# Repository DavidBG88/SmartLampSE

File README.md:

# **SmartLampSE**

## **Overview**
This repository contains the code for the Smart Lamp EmbeddedSystem (SmartLampSE) project. The project involves designing and implementing a smart lamp system using various technologies and programming languages.

## **Features**
- **Electronics Design**: Schematics and PCB design for the smart lamp hardware.
- **Software**: Code for controlling the smart lamp, including firmware and higher-level software.
- **System Model**: Models and diagrams illustrating the system architecture and behavior.

## **Structure**
- **electronics_design/**: Contains schematics and PCB design files.
- **software/**: Source code for the smart lamp, including firmware and application software.
- **system_model/**: System architecture models and documentation.
- **.gitignore**: Git ignore file for the repository.

## **Contributors**
- [DavidBG88](https://github.com/DavidBG88)
- [Tikitikitikidesuka](https://github.com/Tikitikitikidesuka)

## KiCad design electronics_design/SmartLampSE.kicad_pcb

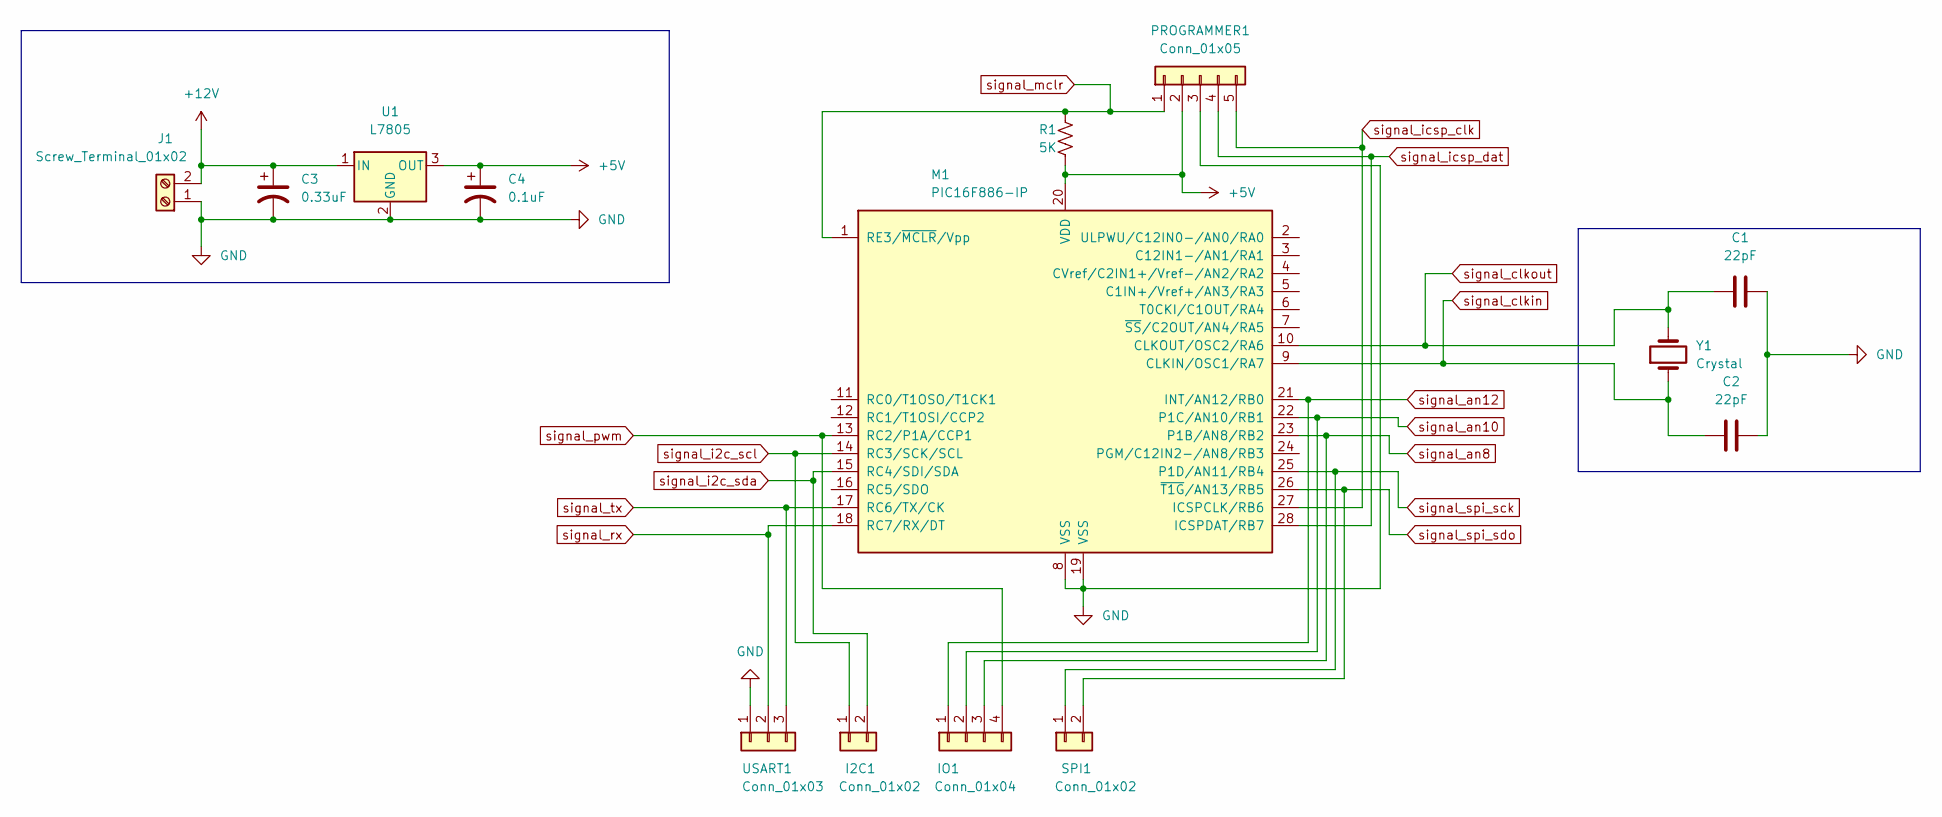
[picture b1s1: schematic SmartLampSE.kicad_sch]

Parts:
C1, C2: 22pF; C_Disc_D3.8mm_W2.6mm_P2.50mm
C3: 0.33uF; CP_Radial_D5.0mm_P2.50mm
C4: 0.1uF; CP_Radial_D5.0mm_P2.50mm
I2C1: Conn_01x02; PinSocket_1x02_P2.54mm_Vertical
IO1: Conn_01x04; PinSocket_1x04_P2.54mm_Vertical
J1: Screw_Terminal_01x02; TerminalBlock_Phoenix_MKDS-1,5-2-5.08_1x02_P5.08mm_Horizont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
M1: PIC16F886-IP; DIP-28_W7.62mm
PROGRAMMER1: Conn_01x05; PinSocket_1x05_P2.54mm_Vertical
R1: 5K; R_Axial_DIN0204_L3.6mm_D1.6mm_P5.08mm_Horizontal
SPI1: Conn_01x02; PinSocket_1x02_P2.54mm_Vertical
U1: L7805; TO-220-3_Vertical
USART1: Conn_01x03; PinSocket_1x03_P2.54mm_Vertical
Y1: Crystal; Crystal_HC18-U_Vertical

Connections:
+5V: C4.1, M1.20 (VDD), PROGRAMMER1.2, R1.2, U1.3 (OUT)
+12V: C3.1, J1.2, U1.1 (IN)
GND: C1.2, C2.2, C3.2, C4.2, J1.1, M1.8 (VSS), M1.19 (VSS), PROGRAMMER1.3, U1.2 (GND), USART1.1
signal_an8: IO1.3, M1.23 (P1B/AN8/RB2)
signal_an10: IO1.2, M1.22 (P1C/AN10/RB1)
signal_an12: IO1.1, M1.21 (INT/AN12/RB0)
signal_clkin: C2.1, M1.9 (CLKIN/OSC1/RA7), Y1.1
signal_clkout: C1.1, M1.10 (CLKOUT/OSC2/RA6), Y1.2
signal_i2c_scl: I2C1.1, M1.14 (RC3/SCK/SCL)
signal_i2c_sda: I2C1.2, M1.15 (RC4/SDI/SDA)
signal_icsp_clk: M1.27 (ICSPCLK/RB6), PROGRAMMER1.5
signal_icsp_dat: M1.28 (ICSPDAT/RB7), PROGRAMMER1.4
signal_mclr: M1.1 (RE3/~MCLR/Vpp), PROGRAMMER1.1, R1.1
signal_pwm: IO1.4, M1.13 (RC2/P1A/CCP1)
signal_rx: M1.18 (RC7/RX/DT), USART1.2
signal_spi_sck: M1.25 (P1D/AN11/RB4), SPI1.1
signal_spi_sdo: M1.26 (~T1G/AN13/RB5), SPI1.2
signal_tx: M1.17 (RC6/TX/CK), USART1.3

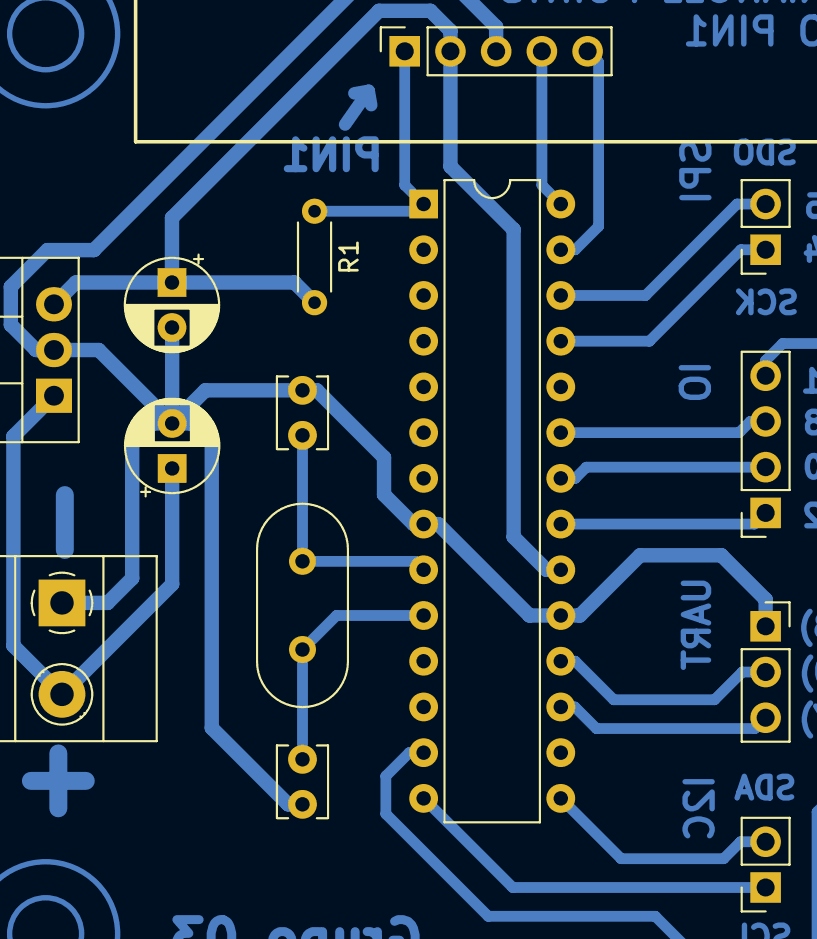
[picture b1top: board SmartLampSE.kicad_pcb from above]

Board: 2 copper layers, 14 parts (0 on the bottom side), 18 nets.

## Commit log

2023-11-05 Add empty Papyrus Sysml project
2023-11-06 Separate board IO interface
2023-11-06 Fix lock files
2023-11-06 Finish pcb pathing
2023-11-07 Update group name on electronics design
2023-11-09 Add visual polarity indicators to board supply
2023-11-10 Fix some widths
2023-11-10 Add MPLab IDE ignored files
2023-11-10 Add MPLab project
2023-11-10 Update gitignore for MPLab projects
2023-11-11 Update pwm library
2023-11-11 Add clang-format file
2023-11-16 Update project model
2023-11-16 Add port connections to system model
2023-11-16 Fix wrong arrow direction in model
2023-11-16 Update ocnnector names in model
2023-11-16 Update model
2023-11-16 Fix typos in pwm header file
2023-11-16 Remove board test libraries
2023-11-16 Update gitignore for new production directory
2023-11-16 Add production smart_lamp_se project
2023-11-16 Added Design.png to electronic Design
2023-11-16 Added tests to main.c for ADC and USART, also notes for I2C future tests
2023-11-17 Fill untested timing implementation
2023-11-18 Fix timing module
2023-11-18 Add State Machine Diagram for controller block
2023-11-18 Update SMD_Controller model
2023-11-18 Refactor model file structure
2023-11-18 Update system model
2023-11-22 Add ADC module
2023-11-22 Fix adc type warning
2023-11-22 Add uart module
2023-11-29 Update state machine in SysML model
2023-11-30 Update uart library
2023-12-01 Update main program
2023-12-01 Fix uart last byte missing error
2023-12-01 Update interrupt flag update policy
2023-12-01 Added I2C test to board_test
2023-12-01 VOID
2023-12-01 Update uart module
2023-12-01 Update UART to remove unnecessary code
2023-12-03 Add i2c library
2023-12-03 Add library for the iAQ-Core sensor
2023-12-03 Add spi library
2023-12-03 Add APA102 RGB LED library
2023-12-03 Add new library files to MPLAB project
2023-12-03 Update ADC module to take adc pin as parameter
2023-12-03 Fix APA102.h include guards
2023-12-03 Add i2c init function
2023-12-03 Remove hyphen from iAQCore library file names
2023-12-03 Update main to follow previous changes
2023-12-03 Add EEPROM memory module
2023-12-03 Add EEPROM library to MPLAB project
2023-12-03 Fix missing void in function parameters
2023-12-03 Rename ADC methods as part of a general refactor
2023-12-03 Remove unnecessary static keyword usages
2023-12-03 Fix repeated function name in adc module
2023-12-03 Rename i2c methods as part of a general refactor
2023-12-03 Rename iAQCore methods as part of a general refactor
2023-12-03 Rename PWM methods as part of a general refactor
2023-12-03 Rename SPI methods as part of a general refactor
2023-12-03 Rename timing methods as part of a general refactor
2023-12-03 Rename UART methods as part of a general refactor
2023-12-04 Update main to allow test selection
2023-12-04 Add uart tx test source files
2023-12-04 Major refactor to board test project
2023-12-04 Fill in pwm, uart rx and uart tx tests
2023-12-04 Fix missing start and end frame in APA102 library
2023-12-04 Update main comment
2023-12-04 Set pickit as target
2023-12-04 Add python client tool
2023-12-07 Add initial web interface
2023-12-08 Upgrade web interface to show sensor values
2023-12-08 Add some requirements to the system model
2023-12-08 Update requirement models
2023-12-09 Update system model main block definition diagram
2023-12-09 Finish SmartLampSE block definition diagram
2023-12-14 Add detailed UARt Activity Diagrams
2023-12-14 Add Timing Activity Diagrams
2023-12-14 Add PWM detailed Activity Diagrams
2023-12-14 Add EEPROM detailed Activity Diagrams
2023-12-14 Add ADC detailed Activity Diagrams
2023-12-14 Add iAQCore detailed Activity Diagrams
2023-12-14 Add main program detailed activity diagrams
2023-12-15 Update main lamp software
2023-12-15 Update web interface
2023-12-15 Update model bugs
2023-12-18 Update software hal libraries
2023-12-20 Update lamp software to send co2 readings
2023-12-20 Update gui interface
2023-12-20 Fix actuator commands
2023-12-20 Add HIH4000 library
2023-12-20 Add LM35 library
2023-12-20 Add VEML7700 library
2023-12-20 Fix mismatch typo on I2C_restart header
2023-12-20 Add web_interface files to gitignore
2023-12-20 Add new sensor libraries to main project
2023-12-20 Add EEPROM config to sma-lamp component
2023-12-21 Update HIH4000 library
2023-12-21 Update APA102 library mode
2023-12-21 Update LM35 library
2023-12-21 Update VEML7700 library mode
2023-12-21 Move ADC VREF and RESOLUTION constants to adc.h
2023-12-21 Update EEPROM library to fix infinite loop glitch
2023-12-21 Add read_n_bytes_reverse function to i2c module
2023-12-21 Fix pwm to return correct max duty cycle value
2023-12-21 Fix incorrect endianness in i2c iAQ-Core sensor reading
2023-12-21 Update spi module mode
2023-12-21 Update timing module mode
2023-12-21 Update uart module mode
2023-12-21 Include previous commits changes to main.c
2023-12-21 Fix sound transform in web gui
2023-12-21 Remove empty xd file
2023-12-21 Update sma-lamp board test libraries to match the ones in smart_lamp_se
